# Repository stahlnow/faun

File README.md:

_FAUN - Feedback Audio Network_
===============================

Collection of things made for the FAUN project.

- Monophonic [amplifier](amplifier)
- 3d printable film [holder](3d)

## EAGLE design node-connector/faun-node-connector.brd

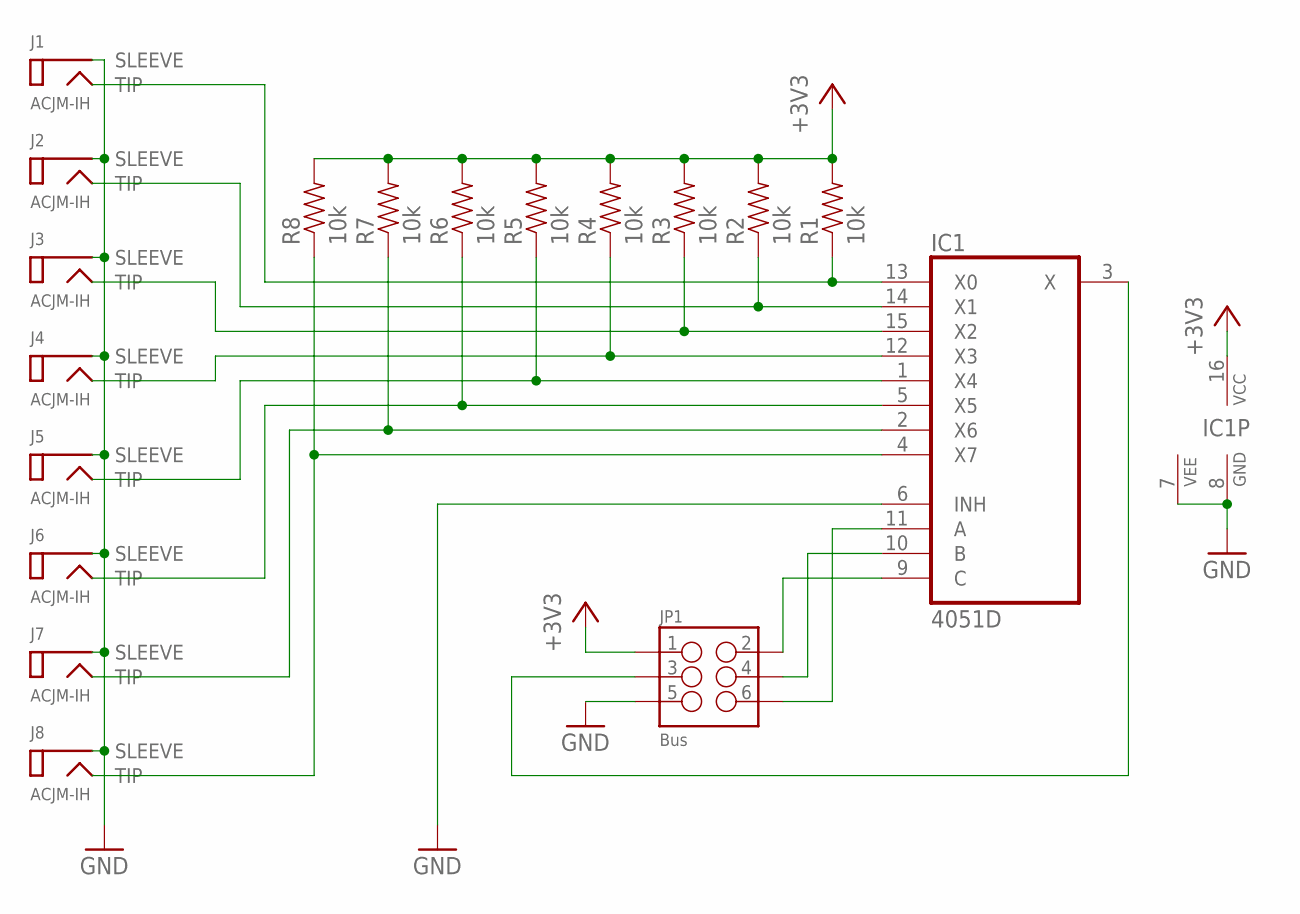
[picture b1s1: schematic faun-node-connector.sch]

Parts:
IC1: 4051D; SO16
J1, J2, J3, J4, J5, J6, J7, J8: ACJM-IH
JP1: Bus; 2X3
R1, R2, R3, R4, R5, R6, R7, R8: 10k; 1206

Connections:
GND: IC1.6 (INH), IC1.7 (VEE), IC1.8 (GND), J1.SLEEVE@1 (SLEEVE), J1.SLEEVE@2 (SLEEVE), J2.SLEEVE@1 (SLEEVE), J2.SLEEVE@2 (SLEEVE), J3.SLEEVE@1 (SLEEVE), J3.SLEEVE@2 (SLEEVE), J4.SLEEVE@1 (SLEEVE), J4.SLEEVE@2 (SLEEVE), J5.SLEEVE@1 (SLEEVE), J5.SLEEVE@2 (SLEEVE), J6.SLEEVE@1 (SLEEVE), J6.SLEEVE@2 (SLEEVE), J7.SLEEVE@1 (SLEEVE), J7.SLEEVE@2 (SLEEVE), J8.SLEEVE@1 (SLEEVE), J8.SLEEVE@2 (SLEEVE), JP1.5
unnamed: IC1.13 (X0), J1.TIP@1 (TIP), J1.TIP@2 (TIP), R1.1
unnamed: IC1.14 (X1), J2.TIP@1 (TIP), J2.TIP@2 (TIP), R2.1
unnamed: IC1.15 (X2), J3.TIP@1 (TIP), J3.TIP@2 (TIP), R3.1
unnamed: IC1.12 (X3), J4.TIP@1 (TIP), J4.TIP@2 (TIP), R4.1
unnamed: IC1.1 (X4), J5.TIP@1 (TIP), J5.TIP@2 (TIP), R5.1
unnamed: IC1.5 (X5), J6.TIP@1 (TIP), J6.TIP@2 (TIP), R6.1
unnamed: IC1.2 (X6), J7.TIP@1 (TIP), J7.TIP@2 (TIP), R7.1
unnamed: IC1.4 (X7), J8.TIP@1 (TIP), J8.TIP@2 (TIP), R8.1
unnamed: IC1.9 (C), JP1.2
unnamed: IC1.10 (B), JP1.4
unnamed: IC1.11 (A), JP1.6
unnamed: IC1.3 (X), JP1.3
VCC: IC1.16 (VCC), JP1.1, R1.2, R2.2, R3.2, R4.2, R5.2, R6.2, R7.2, R8.2

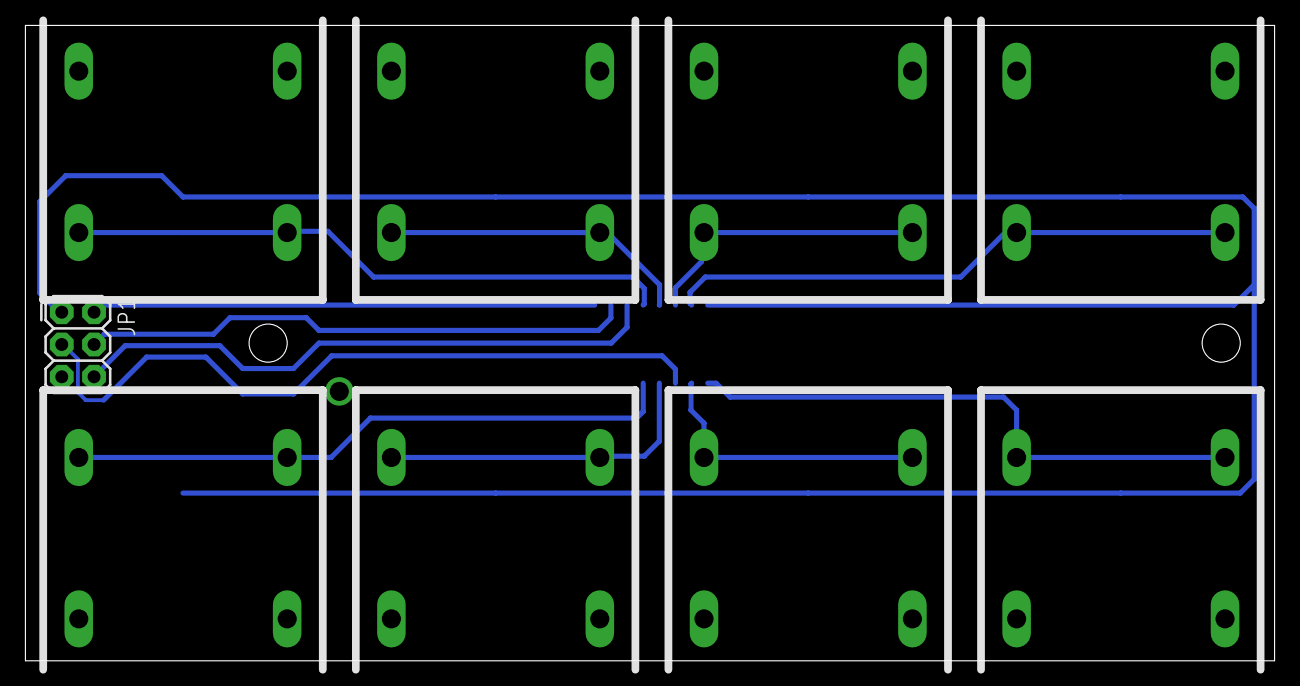
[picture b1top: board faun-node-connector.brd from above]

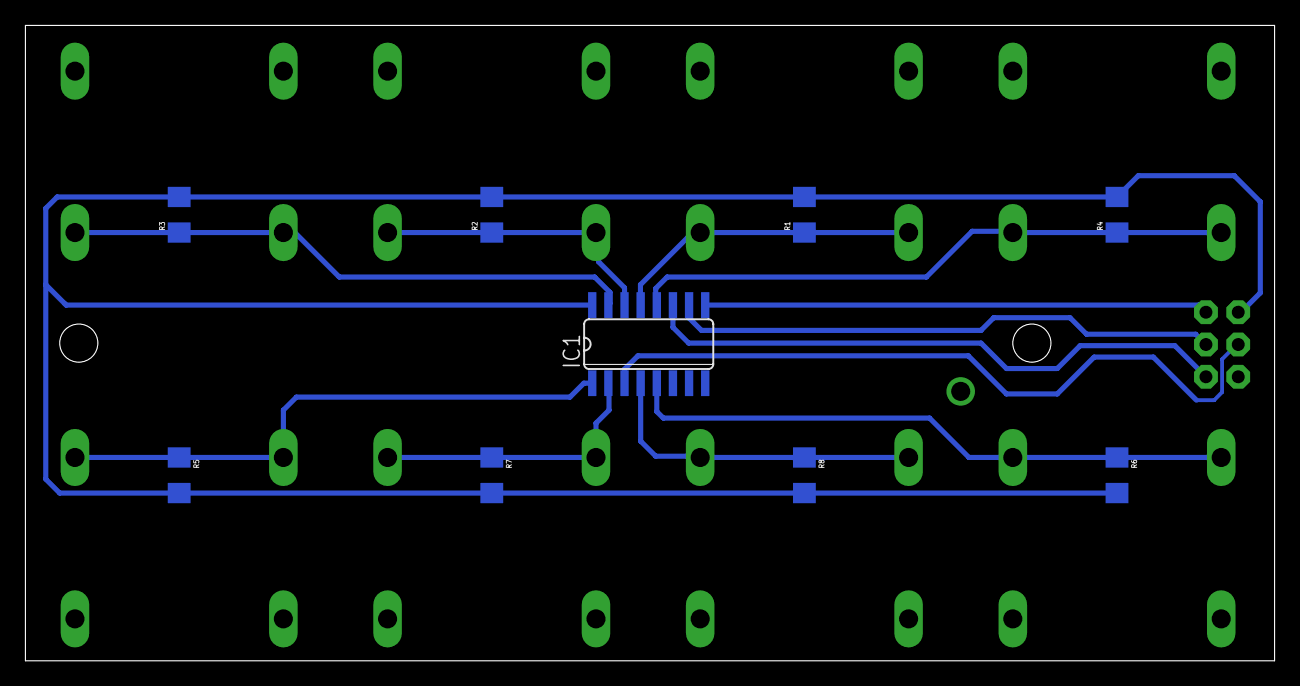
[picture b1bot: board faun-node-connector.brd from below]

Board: 2 copper layers, 98.3 x 50.0 mm, 18 parts (9 on the bottom side), 14 nets.

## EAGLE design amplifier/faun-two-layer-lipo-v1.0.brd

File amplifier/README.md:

Amplifier
=========

Monophonic Audio Amplifier based on the TPA3116D2.

_This file is part of the FAUN project._

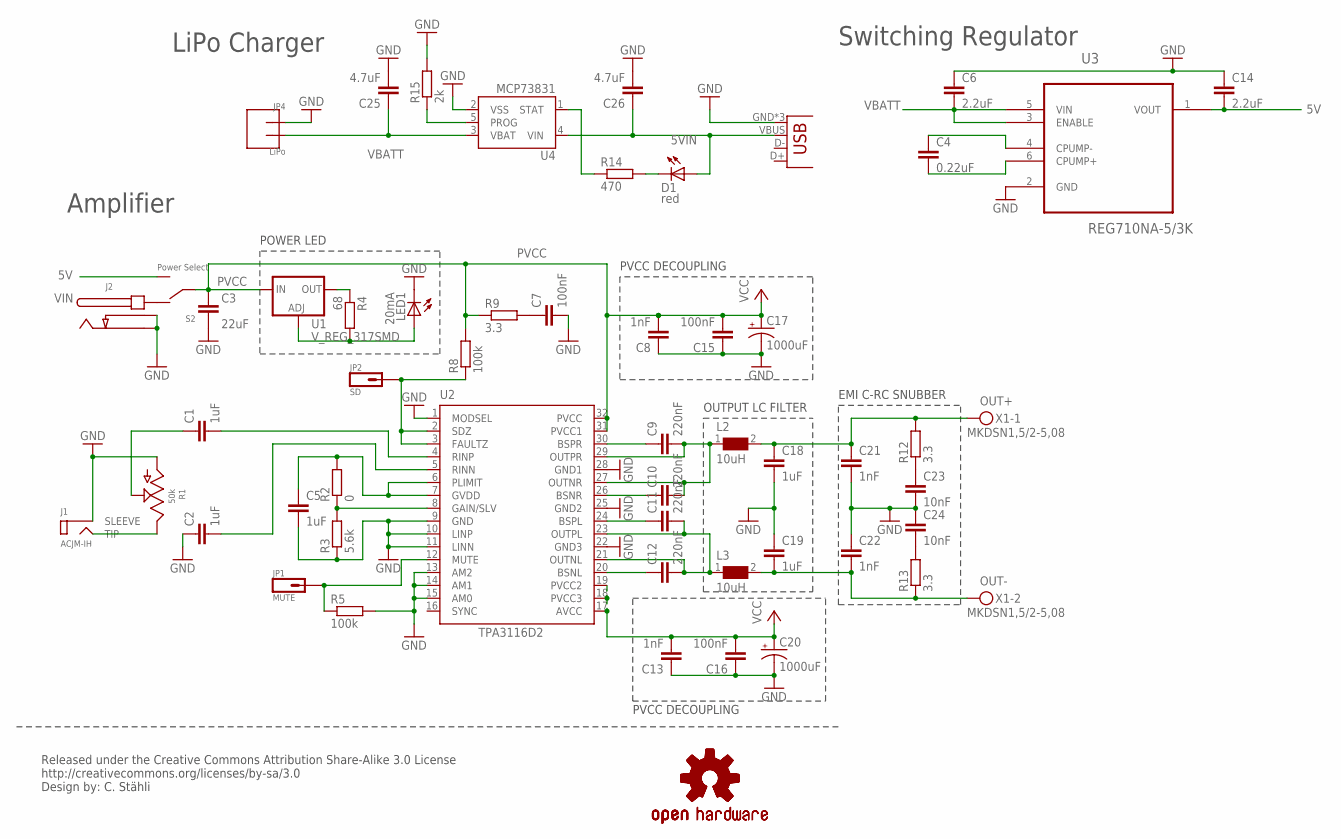
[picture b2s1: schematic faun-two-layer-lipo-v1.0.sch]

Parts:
C1, C2, C5, C18, C19: 1uF; C1206
C3: 22uF; C1206
C4: 0.22uF; C1206
C6, C14: 2.2uF; C1206
C7, C15, C16: 100nF; C1206
C8, C13, C21, C22: 1nF; C1206
C9, C10, C11, C12: 220nF; C1206
C17, C20: 1000uF; UES1E102MHM
C23, C24: 10nF; C1206
C25, C26: 4.7uF; C1206
D1: red; LED-1206
J1: ACJM-IH
J2: PJ-102AH
JP1: MUTE; PAD-1.5X4.5
JP2: SD; PAD-1.5X4.5
JP4: LiPo; 1778764
L2, L3: 10uH; WE-PD_1260/1245/1280/1210
LED1: 20mA; LED-1206
OPEN_HARDWARE_LOGO: OSHW-LOGOL; OSHW-LOGO-L
OPEN_HARDWARE_LOGO_TOP: OSHW-LOGOL; OSHW-LOGO-L
R1: 50k; PTD902-2015K
R2: 0; R1206
R3: 5.6k; R1206
R4: 68; R1206
R5, R8: 100k; R1206
R9, R12, R13: 3.3; R1206
R14: 470; R1206
R15: 2k; R1206
S2: Power Select; MS-100845
U1: V_REG_317SMD; SOT223
U2: TPA3116D2
U3: REG710NA-5/3K; SOT95P280X145-6N
U4: MCP73831; SOT23-5
X1: MKDSN1,5/2-5,08
X2: USB-MICROB

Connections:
5V: C14.2, S2.P$3, U3.1 (VOUT)
5VIN: C26.1, D1.A, U4.4 (VIN), X2.VBUS
GND: C2.1, C3.2, C5.2, C6.1, C7.2, C8.1, C13.1, C14.1, C15.1, C16.1, C17.-, C18.2, C19.1, C20.-, C21.2, C22.1, C23.2, C24.1, C25.2, C26.2, J1.SLEEVE@1 (SLEEVE), J1.SLEEVE@2 (SLEEVE), J2.GND@1, J2.GND@2, JP4.1, LED1.C, R1.1, R1.1' (1), R3.1, R5.2, R15.2, U2.1 (MODSEL), U2.9 (GND), U2.10 (LINP), U2.11 (LINN), U2.13 (AM2), U2.14 (AM1), U2.15 (AM0), U2.22 (GND3), U2.25 (GND2), U2.28 (GND1), U3.2 (GND), U4.2 (VSS), X2.GND, X2.MT1 (GND), X2.MT2 (GND)
MUTE: JP1.P$1, R5.1, U2.12 (MUTE)
unnamed: C5.1, R2.2, U2.6 (PLIMIT), U2.7 (GVDD)
unnamed: C9.1, U2.30 (BSPR)
unnamed: C2.2, U2.5 (RINN)
unnamed: J1.TIP@1 (TIP), J1.TIP@2 (TIP), R1.3, R1.3' (3)
unnamed: C1.2, U2.4 (RINP)
unnamed: C1.1, R1.2, R1.2' (2)
unnamed: C7.1, R9.2
unnamed: R4.1, U1.2 (OUT)
unnamed: C10.1, U2.26 (BSNR)
unnamed: C9.2, C10.2, L2.1, U2.27 (OUTNR), U2.29 (OUTPR)
unnamed: C11.1, U2.24 (BSPL)
unnamed: LED1.A, R4.2, U1.1 (ADJ)
unnamed: C12.1, U2.20 (BSNL)
unnamed: C11.2, C12.2, L3.1, U2.21 (OUTNL), U2.23 (OUTPL)
unnamed: R2.1, R3.2, U2.8 (GAIN/SLV)
unnamed: R15.1, U4.5 (PROG)
unnamed: C23.1, R12.1
unnamed: C24.2, R13.2
unnamed: R14.1, U4.1 (STAT)
unnamed: D1.C, R14.2
unnamed: C4.1, U3.4 (CPUMP-)
unnamed: C4.2, U3.6 (CPUMP+)
OUT+: C18.1, C21.1, L2.2, R12.2, X1.1
OUT-: C19.2, C22.2, L3.2, R13.1, X1.2
PVCC: C3.1, C8.2, C13.2, C15.2, C16.2, C17.+, C20.+, R8.2, R9.1, S2.P$2 (COMM), U1.3 (IN), U2.17 (AVCC), U2.18 (PVCC3), U2.19 (PVCC2), U2.31 (PVCC1), U2.32 (PVCC)
SD: JP2.P$1, R8.1, U2.2 (SDZ), U2.3 (FAULTZ)
VBATT: C6.2, C25.1, JP4.2, U3.3 (ENABLE), U3.5 (VIN), U4.3 (VBAT)
VIN: J2.VCC, S2.P$1

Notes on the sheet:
Released under the Creative Commons Attribution Share-Alike 3.0 License http://creativecommons.org/licenses/by-sa/3.0 Design by: C. Stähli
PVCC DECOUPLING
OUTPUT LC FILTER
EMI C-RC SNUBBER
LiPo Charger
Switching Regulator
POWER LED
Amplifier

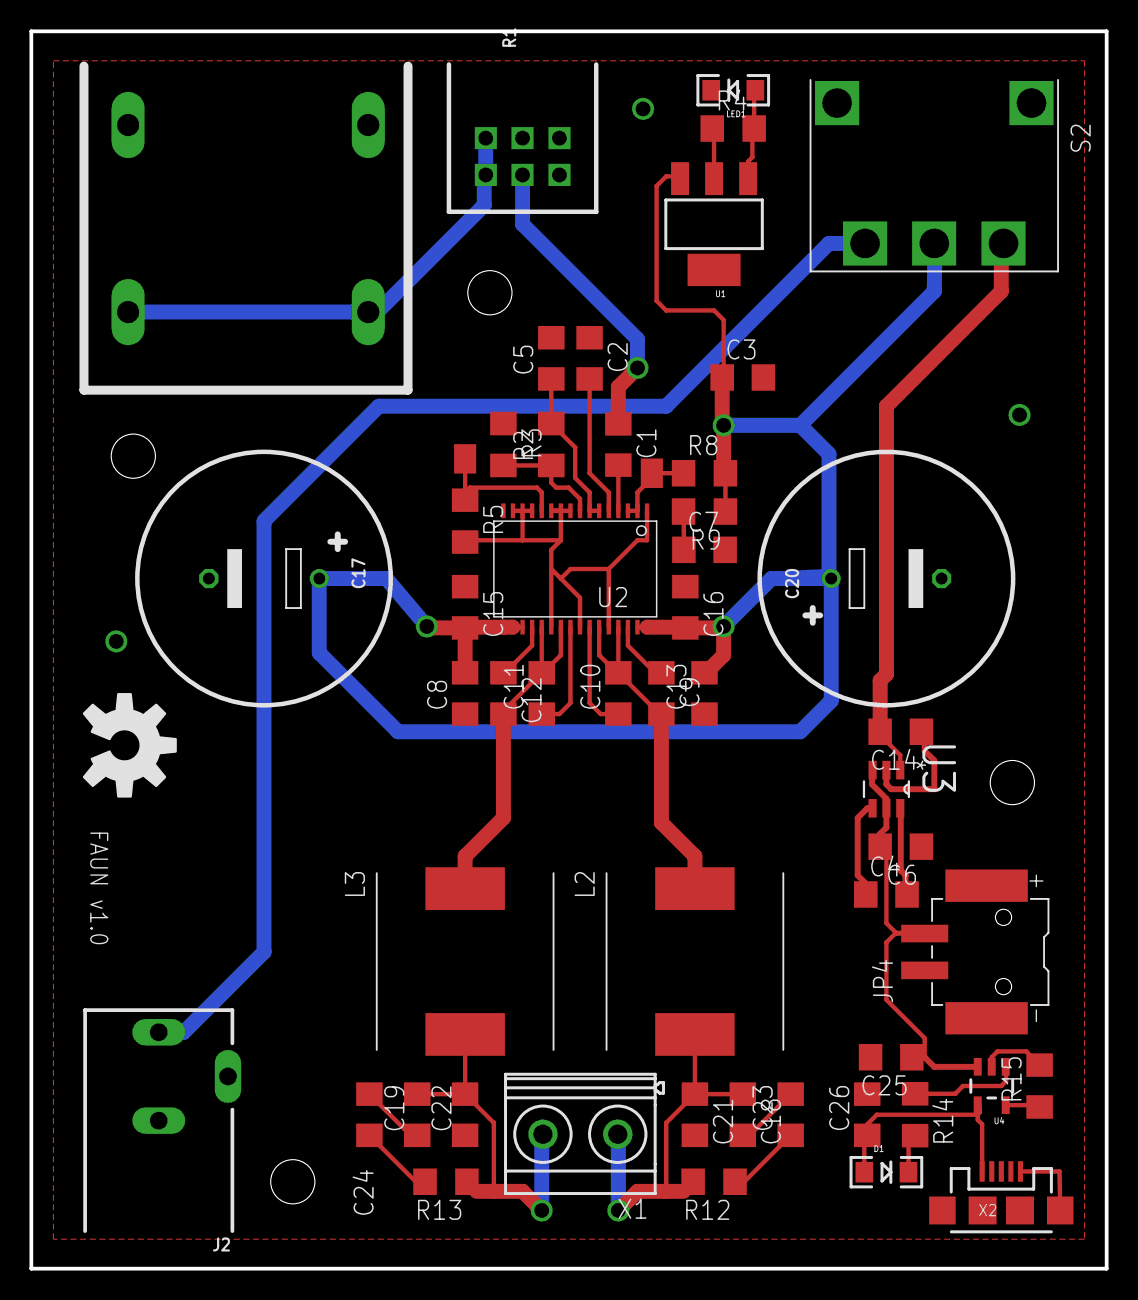
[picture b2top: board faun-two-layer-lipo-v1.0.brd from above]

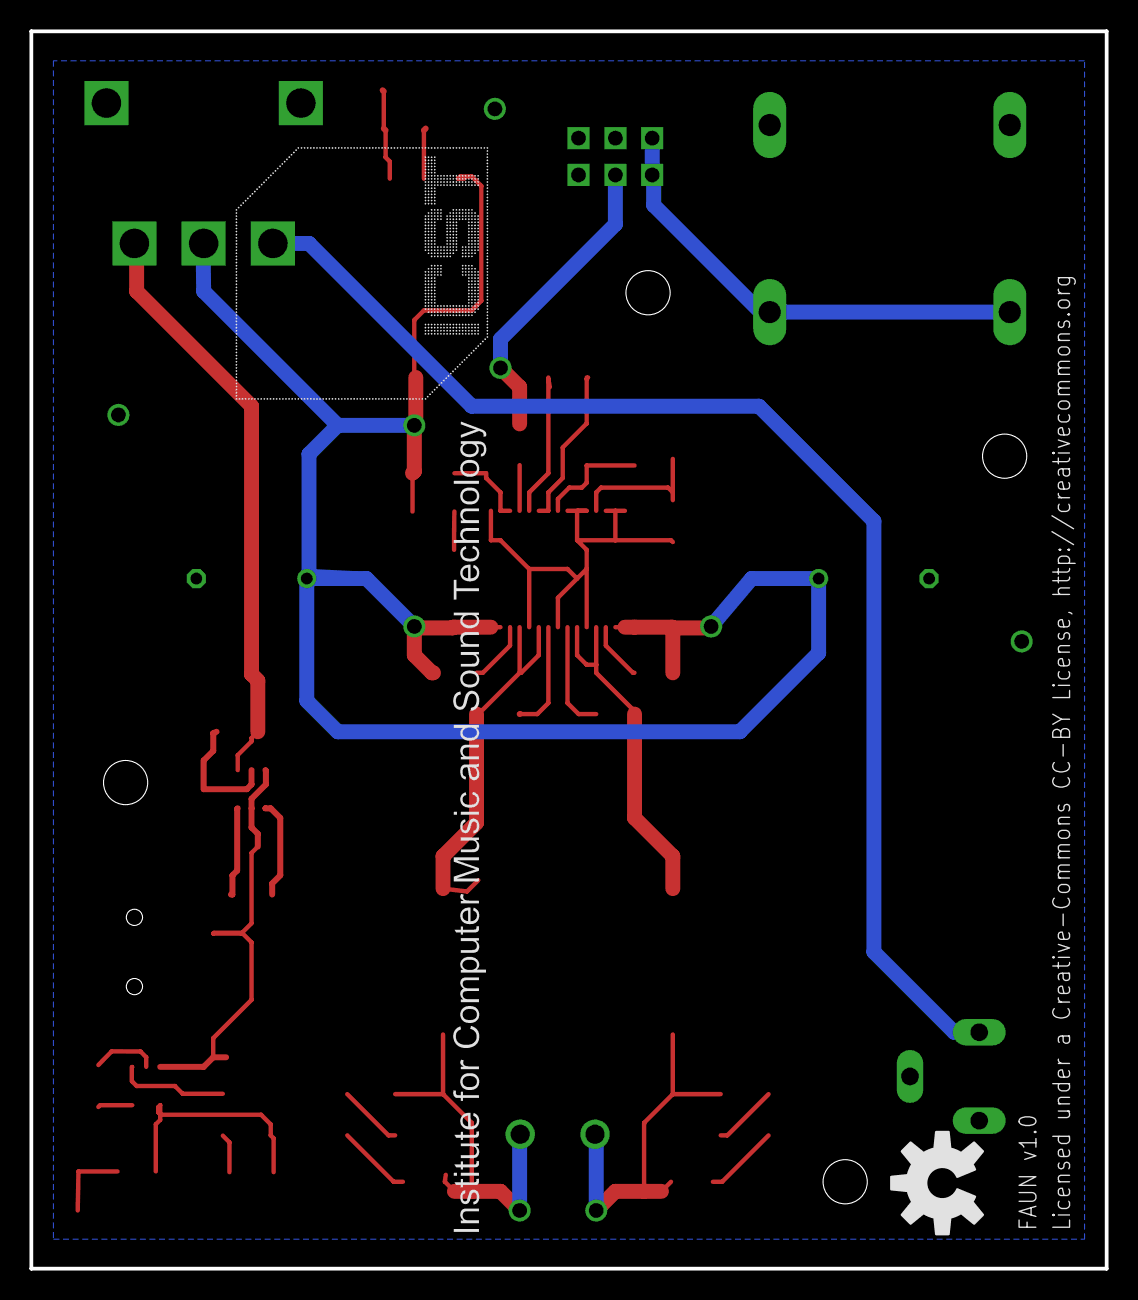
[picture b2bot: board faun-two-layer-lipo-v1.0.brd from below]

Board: 2 copper layers, 73.0 x 84.0 mm, 56 parts (2 on the bottom side), 32 nets.

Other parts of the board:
U$2: ICST-LOGO

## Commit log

2014-06-26 added amplifier eagle files, case and film holder
2015-04-29 updated case
2015-04-29 node connector

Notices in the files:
amplifier/faun-two-layer-lipo-v1.0.brd:
Licensed under a Creative-Commons CC-BY License, http://creativecommons.org
parts and their libraries:
SparkFun-LED: Licensing: CC v3.0 Share-Alike You are welcome to use this library for commercial purposes.
